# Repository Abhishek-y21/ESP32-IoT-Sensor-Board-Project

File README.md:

# ESP32-C3 WROOM-02 Sensor Board

## 📌 Project Overview
This project is a custom PCB designed using KiCad, built around the ESP32-C3 WROOM-02 module.  
It is intended for IoT and sensor-based applications, supporting battery operation, wireless connectivity, and peripheral interfacing.

---

## 🔧 Components Used
- *ESP32-C3 WROOM-02* (Wi-Fi + BLE microcontroller module)  
- *TP4056* (Li-ion / LiPo battery charging IC)  
- *3.3V Voltage Regulator* (AMS1117 or LDO for stable MCU supply)  
- *USB-C Connector* (for power and programming)  
- *LEDs + Resistors* (power and status indication)  
- *Capacitors* (decoupling and filtering)  
- *Optional Sensors* (BME280 for temp/humidity/pressure, light sensor, etc.)  
- *Optional OLED Display* (0.96" I²C module)  
- *SD Card Socket* (for data logging)  

## 🚀 Applications
- IoT Prototyping and Development  
- Environmental Data Logging  
- Wireless Sensor Networks  
- Smart Home Devices  
- Educational Projects in Embedded Systems and PCB Design  

---

## ✍ Author
*Abhishek Yadav*  

---

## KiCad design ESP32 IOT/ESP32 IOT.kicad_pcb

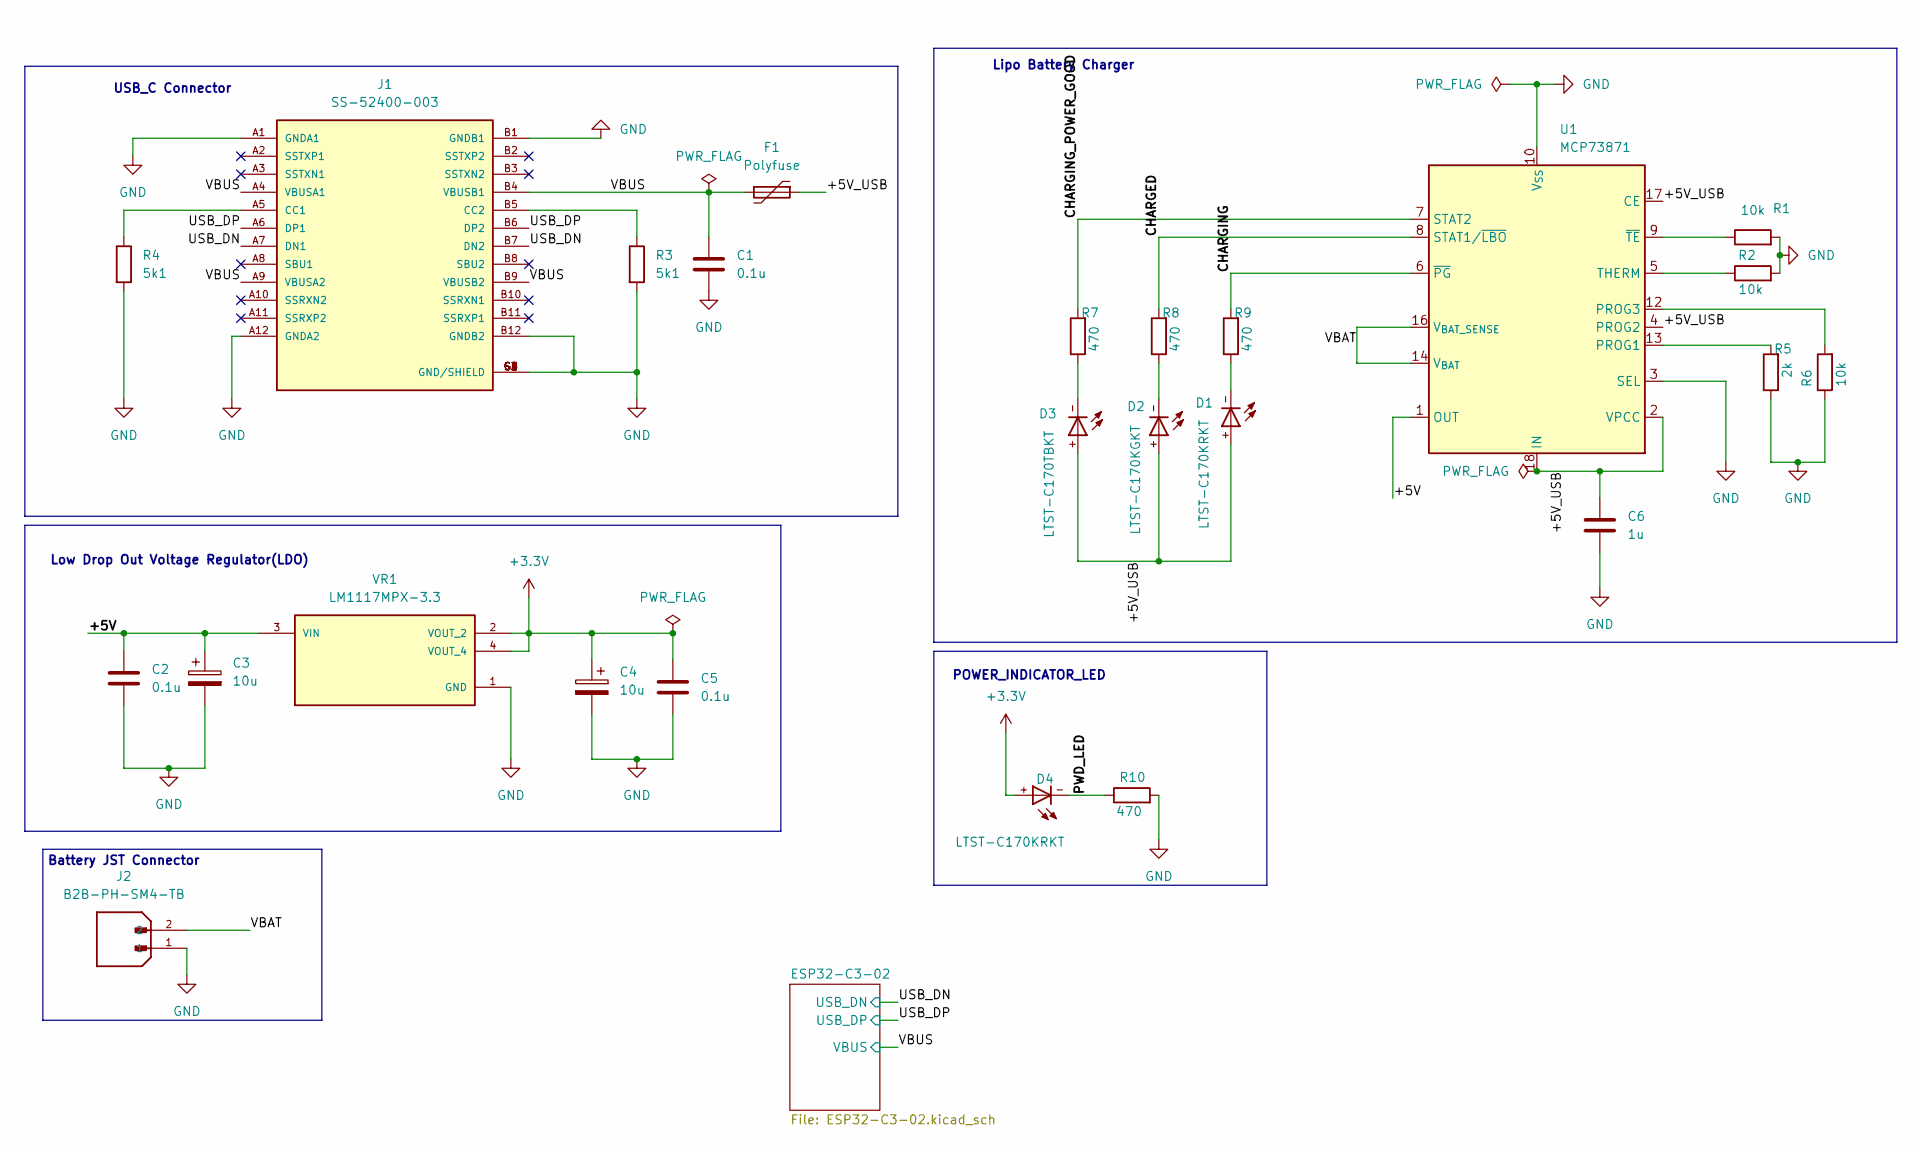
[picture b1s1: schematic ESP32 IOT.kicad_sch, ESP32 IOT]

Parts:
C1, C2, C5: 0.1u; C_0805_2012Metric
C3, C4: 10u; CP_EIA-3528-21_Kemet-B
C6: 1u; C_0805_2012Metric
D1, D4: LTST-C170KRKT; DIOC200X125X110
D2: LTST-C170KGKT; DIOC200X125X110
D3: LTST-C170TBKT; DIOC200X125X110
F1: Polyfuse; R_Radial_Power_L11.0mm_W7.0mm_P5.00mm
J1: SS-52400-003; BELFUSE_SS-52400-003; PARTREV A0
J2: B2B-PH-SM4-TB; JST_B2B-PH-SM4-TB; PARTREV N/A
R1, R2, R6: 10k; R_0805_2012Metric
R3, R4: 5k1; R_0805_2012Metric
R5: 2k; R_0805_2012Metric
R7, R8, R9, R10: 470; R_0805_2012Metric
U1: MCP73871; QFN-20-1EP_4x4mm_P0.5mm_EP2.5x2.5mm
VR1: LM1117MPX-3.3; VREG_LM1117MPX-3.3; PARTREV O

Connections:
+3.3V: C4.1, C5.1, D4.+, VR1.2 (VOUT_2), VR1.4 (VOUT_4); also elsewhere on the board
/+5V: C2.1, C3.1, U1.1 (OUT), U1.20 (OUT), VR1.3 (VIN)
/+5V_USB: C6.1, D1.+, D2.+, D3.+, F1.1, U1.2 (VPCC), U1.4 (PROG2), U1.17 (CE), U1.18 (IN), U1.19 (IN)
/CHARGED: R8.2, U1.8 (STAT1/~LBO)
/CHARGING: R9.2, U1.6 (~PG)
/CHARGING_POWER_GOOD: R7.2, U1.7 (STAT2)
/PWD_LED: D4.-, R10.1
/USB_DN: J1.A7 (DN1), J1.B7 (DN2); also elsewhere on the board
/USB_DP: J1.A6 (DP1), J1.B6 (DP2); also elsewhere on the board
/VBAT: J2.2, U1.14 (V_{BAT}), U1.15 (V_{BAT}), U1.16 (V_{BAT_SENSE})
/VBUS: C1.1, F1.2, J1.A4 (VBUSA1), J1.A9 (VBUSA2), J1.B4 (VBUSB1), J1.B9 (VBUSB2); also elsewhere on the board
GND: C1.2, C2.2, C3.2, C4.2, C5.2, C6.2, J1.A1 (GNDA1), J1.A12 (GNDA2), J1.B1 (GNDB1), J1.B12 (GNDB2), J1.G1 (GND/SHIELD), J1.G2 (GND/SHIELD), J1.G3 (GND/SHIELD), J1.G4 (GND/SHIELD), J1.S1 (GND/SHIELD), J1.S2 (GND/SHIELD), J1.S3 (GND/SHIELD), J1.S4 (GND/SHIELD), J2.1, R1.2, R2.2, R3.2, R4.2, R5.1, R6.1, R10.2, U1.3 (SEL), U1.10 (V_{SS}), U1.11 (V_{SS}), U1.21 (V_{SS}), VR1.1 (GND); also elsewhere on the board
unnamed: D1.-, R9.1
unnamed: D2.-, R8.1
unnamed: D3.-, R7.1
unnamed: J1.A5 (CC1), R4.1
unnamed: J1.B5 (CC2), R3.1
unnamed: R5.2, U1.13 (PROG1)
unnamed: R6.2, U1.12 (PROG3)
unnamed: R2.1, U1.5 (THERM)
unnamed: R1.1, U1.9 (~TE)

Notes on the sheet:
Battery JST Connector
POWER_INDICATOR_LED
Lipo Battery Charger
USB_C Connector
Low Drop Out Voltage Regulator(LDO)

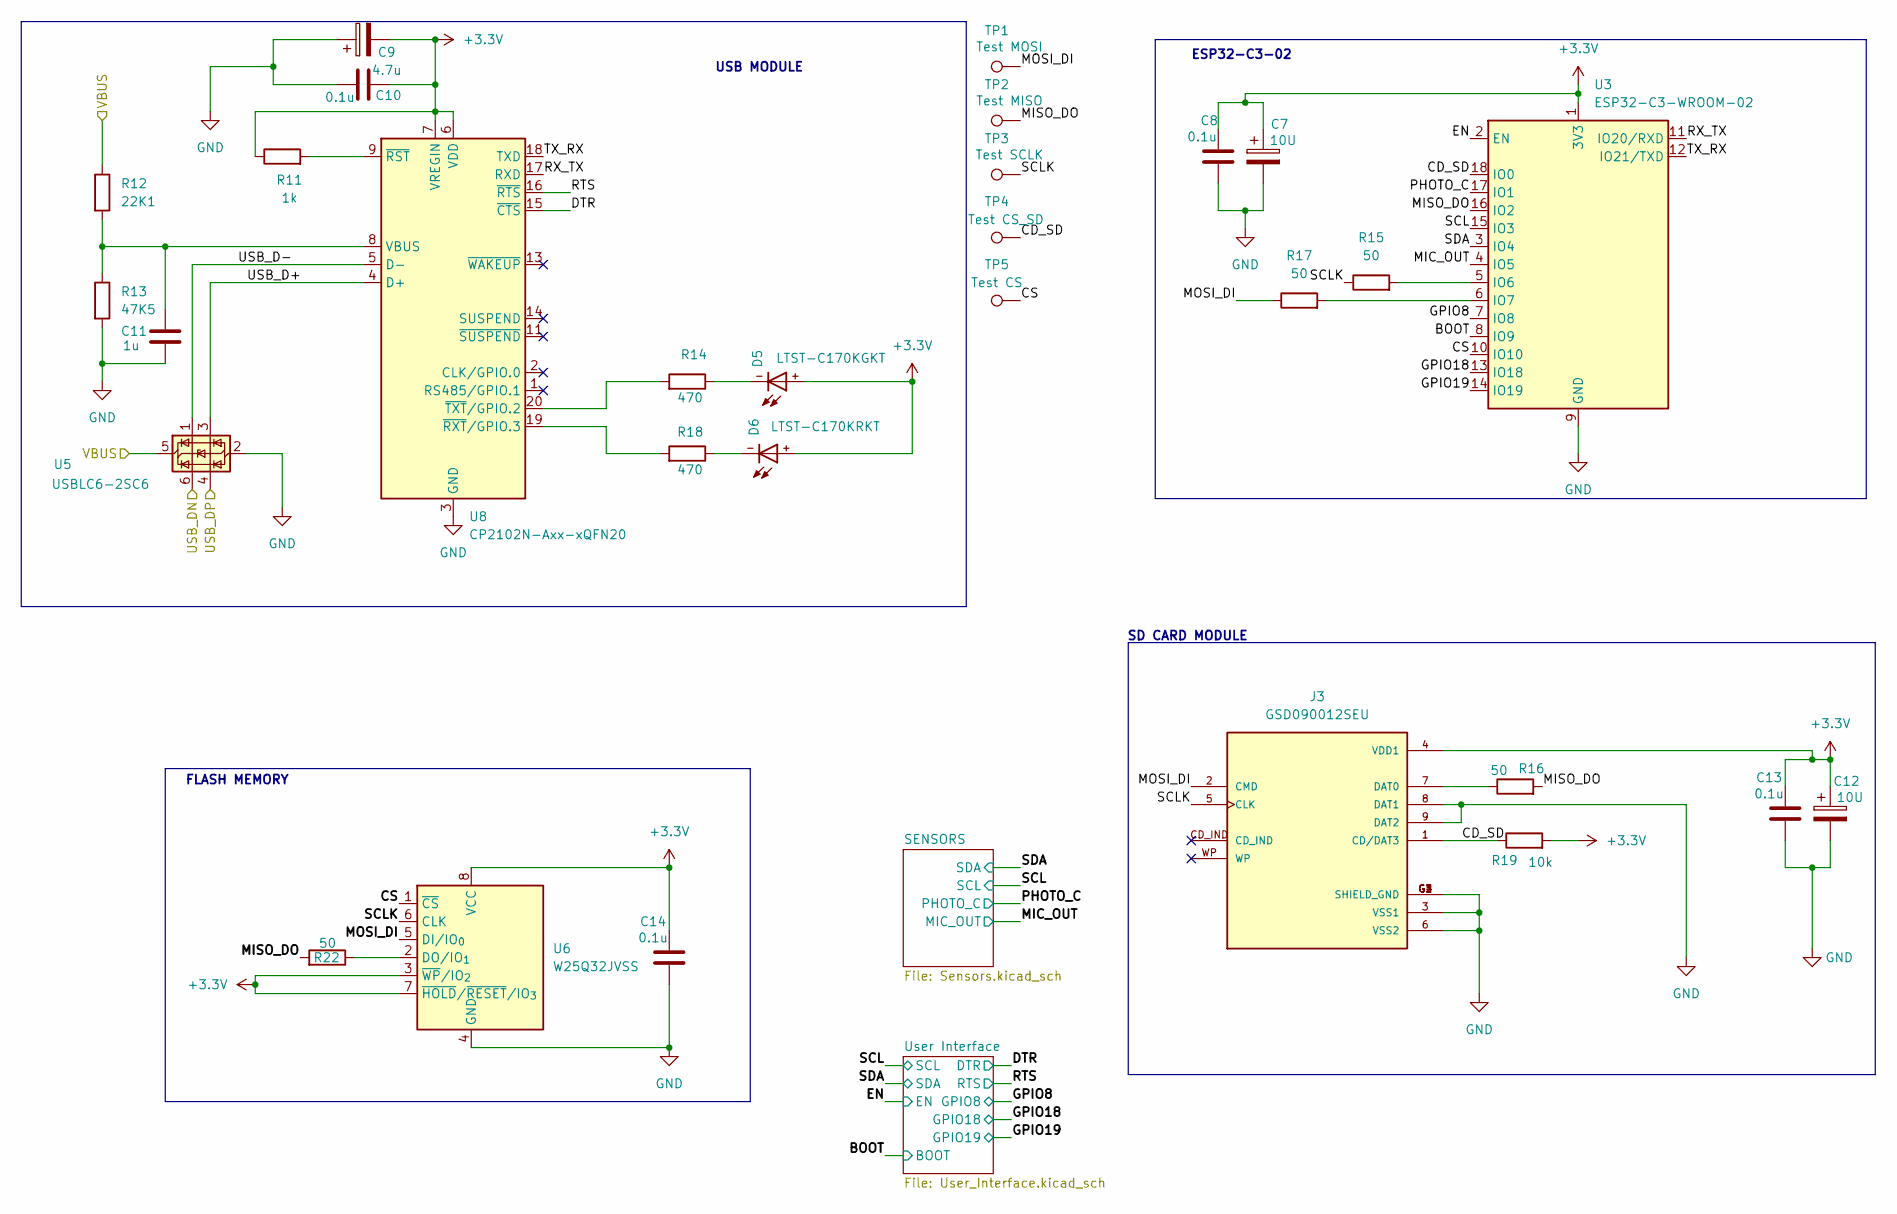
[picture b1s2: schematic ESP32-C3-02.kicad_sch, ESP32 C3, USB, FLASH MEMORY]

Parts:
C7, C12: 10U; CP_EIA-3528-21_Kemet-B
C8, C10, C13, C14: 0.1u; C_0805_2012Metric
C9: 4.7u; CP_EIA-3528-21_Kemet-B
C11: 1u; C_0805_2012Metric
D5: LTST-C170KGKT; DIOC200X125X110
D6: LTST-C170KRKT; DIOC200X125X110
J3: GSD090012SEU; AMPHENOL_GSD090012SEU; PARTREV E
R11: 1k; R_0805_2012Metric
R12: 22K1; R_0805_2012Metric
R13: 47K5; R_0805_2012Metric
R14, R18: 470; R_0805_2012Metric
R15, R16, R17, R22: 50; R_0805_2012Metric
R19: 10k; R_0805_2012Metric
TP1: Test MOSI; TestPoint_Pad_D1.0mm
TP2: Test MISO; TestPoint_Pad_D1.0mm
TP3: Test SCLK; TestPoint_Pad_D1.0mm
TP4: Test CS_SD; TestPoint_Pad_D1.0mm
TP5: Test CS; TestPoint_Pad_D1.0mm
U3: ESP32-C3-WROOM-02
U5: USBLC6-2SC6; SOT-23-6
U6: W25Q32JVSS; SOIC-8_5.3x5.3mm_P1.27mm
U8: CP2102N-Axx-xQFN20; SiliconLabs_QFN-20-1EP_3x3mm_P0.5mm_EP1.8x1.8mm_ThermalVias

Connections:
+3.3V: C7.1, C8.1, C9.2, C10.2, C12.1, C13.1, C14.1, D5.+, D6.+, J3.4 (VDD1), R11.1, R19.2, U3.1 (3V3), U6.3 (~WP/IO_{2}), U6.7 (~HOLD/~RESET/IO_{3}), U6.8 (VCC), U8.6 (VDD), U8.7 (VREGIN); also elsewhere on the board
/ESP32-C3-02/BOOT: U3.8 (IO9); also elsewhere on the board
/ESP32-C3-02/CD_SD: J3.1 (CD/DAT3), R19.1, TP4.1, U3.18 (IO0)
/ESP32-C3-02/CS: TP5.1, U3.10 (IO10), U6.1 (~CS)
/ESP32-C3-02/DTR: U8.15 (~CTS); also elsewhere on the board
/ESP32-C3-02/EN: U3.2 (EN); also elsewhere on the board
/ESP32-C3-02/GPIO8: U3.7 (IO8); also elsewhere on the board
/ESP32-C3-02/GPIO18: U3.13 (IO18); also elsewhere on the board
/ESP32-C3-02/GPIO19: U3.14 (IO19); also elsewhere on the board
/ESP32-C3-02/MIC_OUT: U3.4 (IO5); also elsewhere on the board
/ESP32-C3-02/MISO_DO: R16.2, R22.2, TP2.1, U3.16 (IO2)
/ESP32-C3-02/MOSI_DI: J3.2 (CMD), R17.1, TP1.1, U6.5 (DI/IO_{0})
/ESP32-C3-02/PHOTO_C: U3.17 (IO1); also elsewhere on the board
/ESP32-C3-02/RTS: U8.16 (~RTS); also elsewhere on the board
/ESP32-C3-02/RX_TX: U3.11 (IO20/RXD), U8.17 (RXD)
/ESP32-C3-02/SCL: U3.15 (IO3); also elsewhere on the board
/ESP32-C3-02/SCLK: J3.5 (CLK), R15.1, TP3.1, U6.6 (CLK)
/ESP32-C3-02/SDA: U3.3 (IO4); also elsewhere on the board
/ESP32-C3-02/TX_RX: U3.12 (IO21/TXD), U8.18 (TXD)
/ESP32-C3-02/USB_D+: U5.3 (I/O2), U8.4 (D+)
/ESP32-C3-02/USB_D-: U5.1 (I/O1), U8.5 (D-)
/USB_DN: U5.6 (I/O1); also elsewhere on the board
/USB_DP: U5.4 (I/O2); also elsewhere on the board
/VBUS: R12.1, U5.5 (VBUS); also elsewhere on the board
GND: C7.2, C8.2, C9.1, C10.1, C11.2, C12.2, C13.2, C14.2, J3.3 (VSS1), J3.6 (VSS2), J3.8 (DAT1), J3.9 (DAT2), J3.G1 (SHIELD_GND), J3.G2 (SHIELD_GND), J3.G3 (SHIELD_GND), J3.G4 (SHIELD_GND), R13.2, U3.9 (GND), U3.19 (GND), U5.2 (GND), U6.4 (GND), U8.3 (GND), U8.12 (GND), U8.21 (GND); also elsewhere on the board
unnamed: D5.-, R14.1
unnamed: D6.-, R18.1
unnamed: J3.7 (DAT0), R16.1
unnamed: R15.2, U3.5 (IO6)
unnamed: R17.2, U3.6 (IO7)
unnamed: R22.1, U6.2 (DO/IO_{1})
unnamed: C11.1, R12.2, R13.1, U8.8 (VBUS)
unnamed: R11.2, U8.9 (~RST)
unnamed: R18.2, U8.19 (~RXT/GPIO.3)
unnamed: R14.2, U8.20 (~TXT/GPIO.2)

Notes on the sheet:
SD CARD MODULE
ESP32-C3-02
FLASH MEMORY
USB MODULE

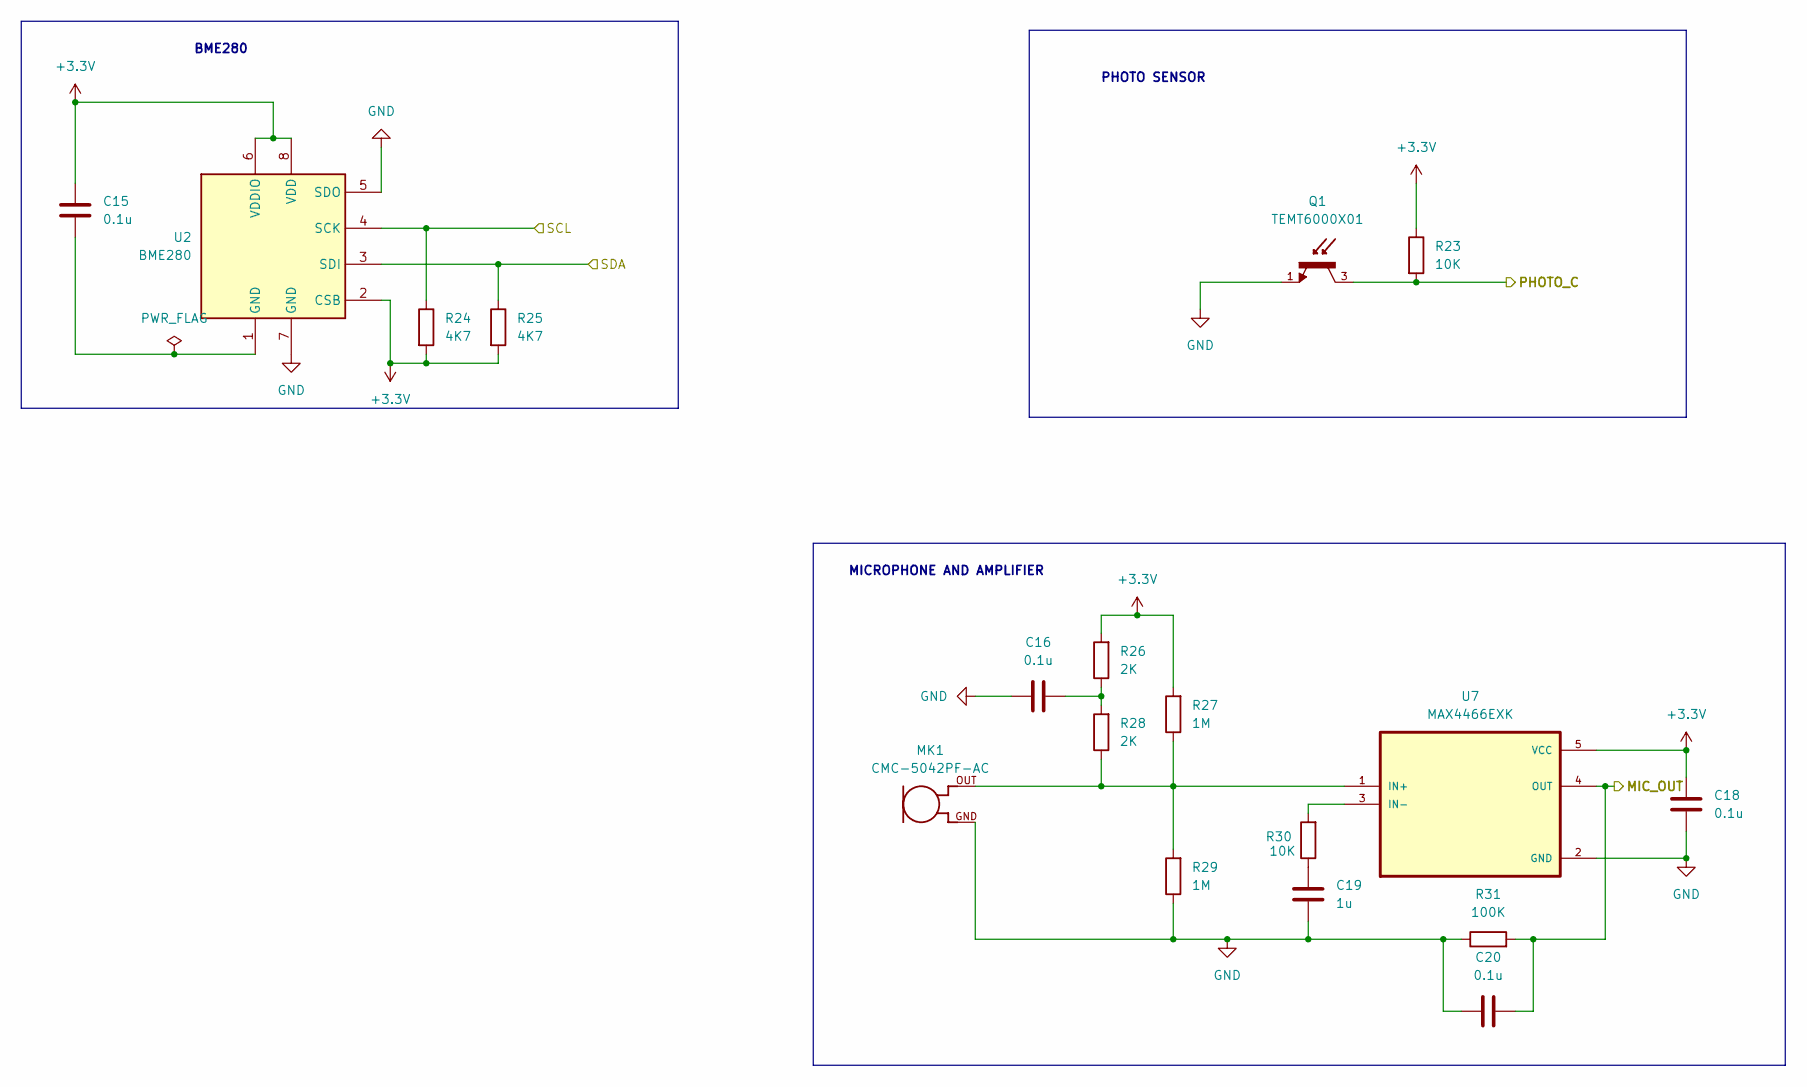
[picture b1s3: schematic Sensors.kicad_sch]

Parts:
C15, C16, C18, C20: 0.1u; C_0805_2012Metric
C19: 1u; C_0805_2012Metric
MK1: CMC-5042PF-AC; CUI_CMC-5042PF-AC
Q1: TEMT6000X01; TRANS_TEMT6000X01; PARTREV 1.9
R23, R30: 10K; R_0805_2012Metric
R24, R25: 4K7; R_0805_2012Metric
R26, R28: 2K; R_0805_2012Metric
R27, R29: 1M; R_0805_2012Metric
R31: 100K; R_0805_2012Metric
U2: BME280; Bosch_LGA-8_2.5x2.5mm_P0.65mm_ClockwisePinNumbering
U7: MAX4466EXK; SOT65P210X110-5N

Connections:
+3.3V: C15.1, C18.1, R23.1, R24.2, R25.2, R26.2, R27.2, U2.2 (CSB), U2.6 (VDDIO), U2.8 (VDD), U7.5 (VCC); also elsewhere on the board
/ESP32-C3-02/MIC_OUT: C20.2, R31.2, U7.4 (OUT); also elsewhere on the board
/ESP32-C3-02/PHOTO_C: Q1.3, R23.2; also elsewhere on the board
/ESP32-C3-02/SCL: R24.1, U2.4 (SCK); also elsewhere on the board
/ESP32-C3-02/SDA: R25.1, U2.3 (SDI); also elsewhere on the board
GND: C16.1, C18.2, C19.1, C20.1, MK1.GND, Q1.1, R29.1, R31.1, U2.5 (SDO), U2.7 (GND), U7.2 (GND); also elsewhere on the board
unnamed: C15.2, U2.1 (GND)
unnamed: C16.2, R26.1, R28.2
unnamed: C19.2, R30.1
unnamed: MK1.OUT, R27.1, R28.1, R29.2, U7.1 (IN+)
unnamed: R30.2, U7.3 (IN-)

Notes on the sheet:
PHOTO SENSOR
BME280
MICROPHONE AND AMPLIFIER

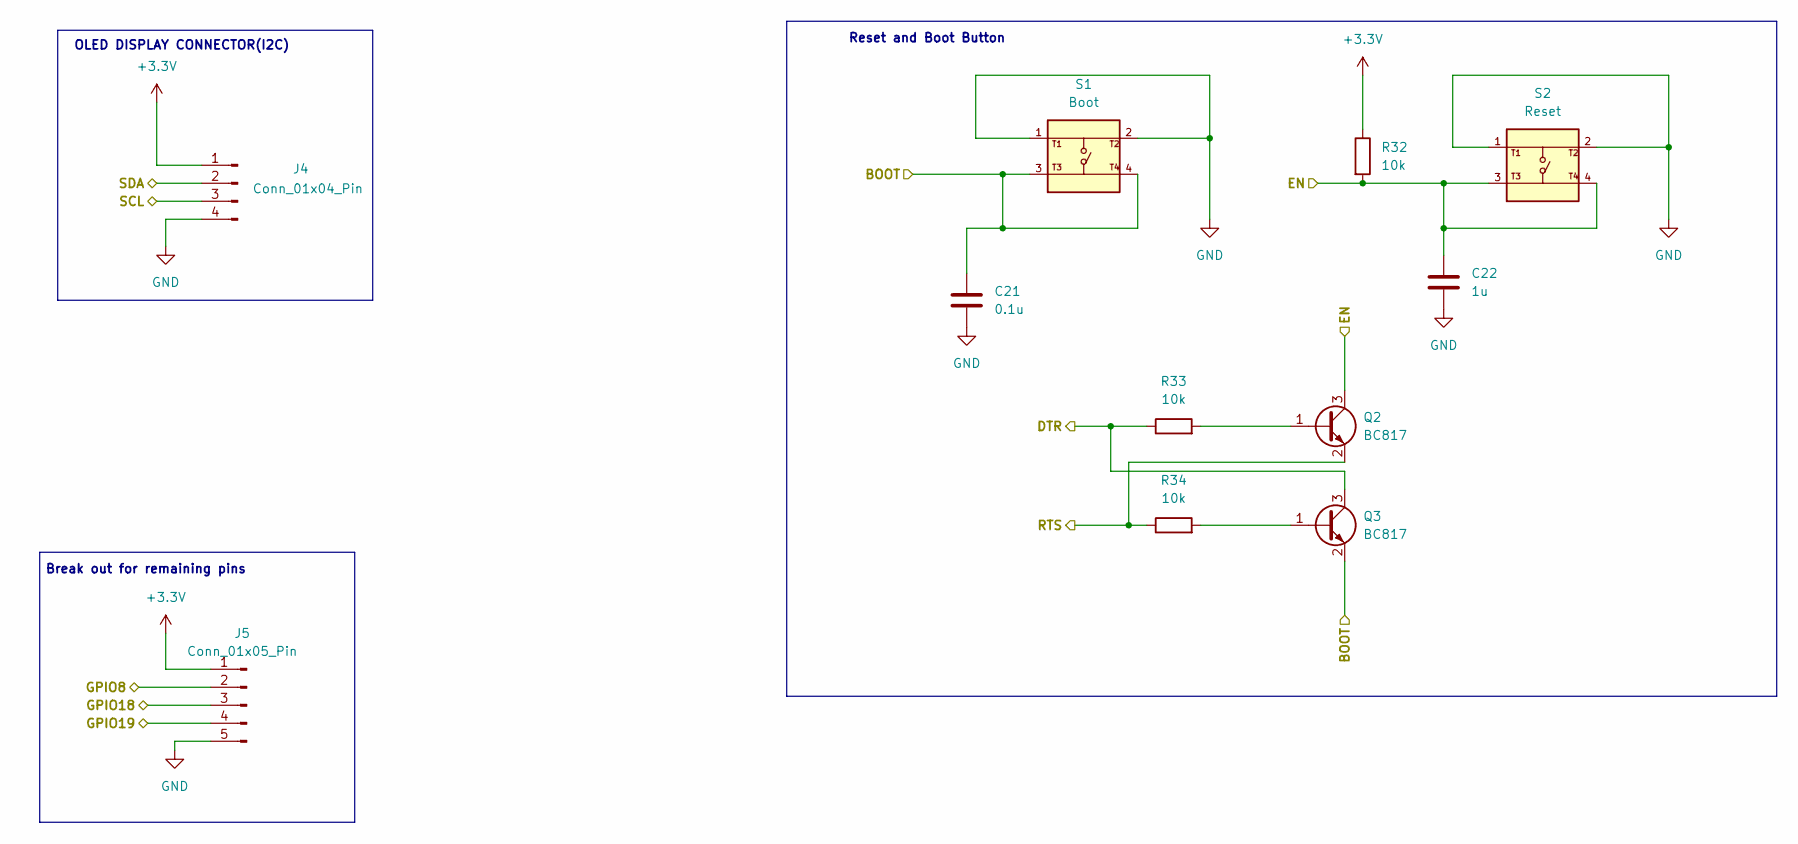
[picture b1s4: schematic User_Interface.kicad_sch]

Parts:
C21: 0.1u; C_0805_2012Metric
C22: 1u; C_0805_2012Metric
J4: Conn_01x04_Pin; PinHeader_1x04_P2.54mm_Vertical
J5: Conn_01x05_Pin; PinHeader_1x05_P2.54mm_Vertical
Q2, Q3: BC817; SOT-23
R32, R33, R34: 10k; R_0805_2012Metric
S1: Boot; SW_USLPT2819DT2TR; PARTREV P
S2: Reset; SW_USLPT2819DT2TR; PARTREV P

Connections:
+3.3V: J4.1, J5.1, R32.1; also elsewhere on the board
/ESP32-C3-02/BOOT: C21.1, Q3.2 (E), S1.3, S1.4; also elsewhere on the board
/ESP32-C3-02/DTR: Q3.3 (C), R33.1; also elsewhere on the board
/ESP32-C3-02/EN: C22.1, Q2.3 (C), R32.2, S2.3, S2.4; also elsewhere on the board
/ESP32-C3-02/GPIO8: J5.2; also elsewhere on the board
/ESP32-C3-02/GPIO18: J5.3; also elsewhere on the board
/ESP32-C3-02/GPIO19: J5.4; also elsewhere on the board
/ESP32-C3-02/RTS: Q2.2 (E), R34.1; also elsewhere on the board
/ESP32-C3-02/SCL: J4.3; also elsewhere on the board
/ESP32-C3-02/SDA: J4.2; also elsewhere on the board
GND: C21.2, C22.2, J4.4, J5.5, S1.1, S1.2, S2.1, S2.2; also elsewhere on the board
unnamed: Q2.1 (B), R33.2
unnamed: Q3.1 (B), R34.2

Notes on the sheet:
Reset and Boot Button
Break out for remaining pins
OLED DISPLAY CONNECTOR(I2C)

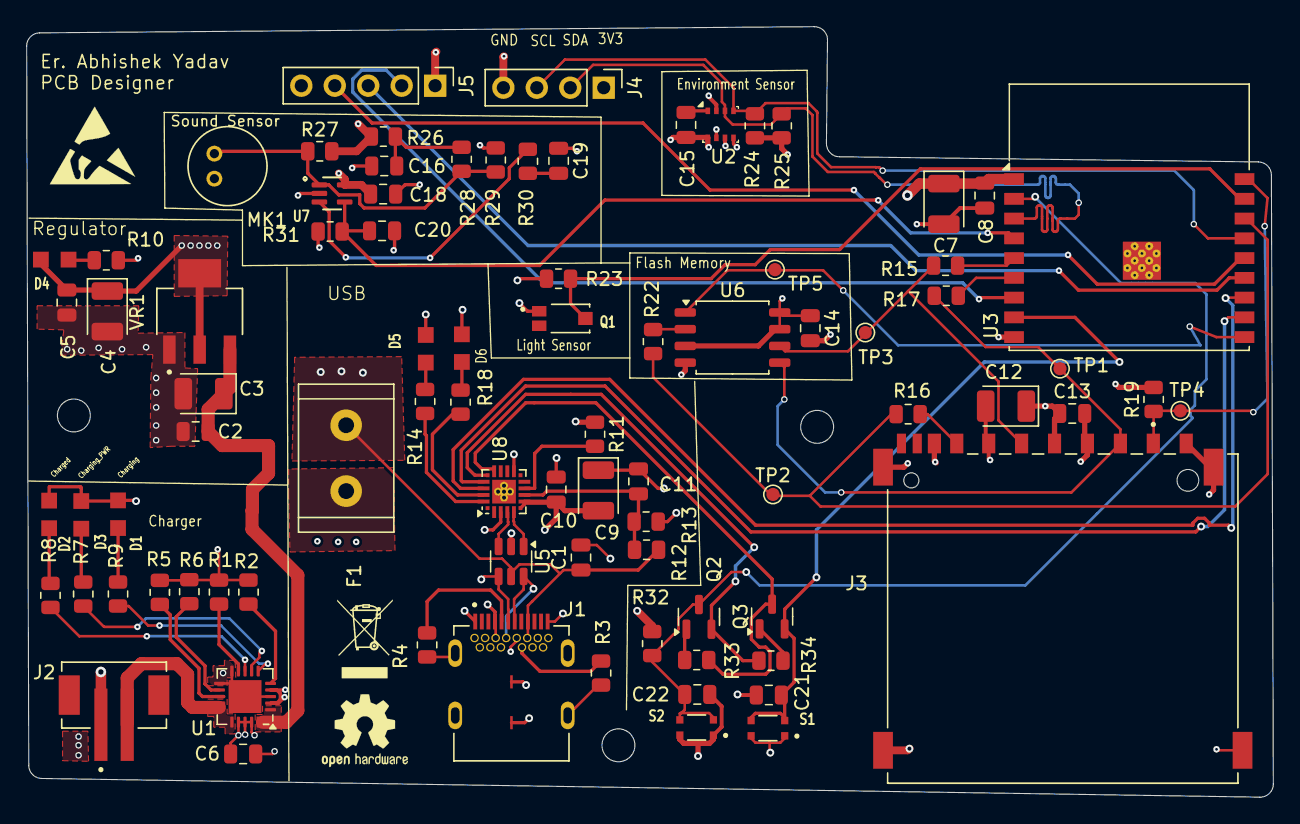
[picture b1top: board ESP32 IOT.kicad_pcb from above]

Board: 4 copper layers, 94.7 x 58.5 mm, 84 parts (0 on the bottom side), 58 nets.

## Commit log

2025-09-14 ESP32
